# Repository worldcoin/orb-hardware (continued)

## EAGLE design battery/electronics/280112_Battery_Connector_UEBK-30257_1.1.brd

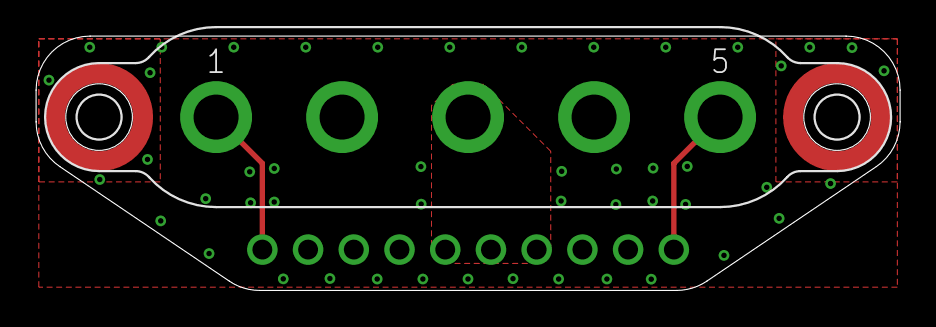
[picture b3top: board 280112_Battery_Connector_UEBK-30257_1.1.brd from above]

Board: 2 copper layers, 48.0 x 14.1 mm, 4 parts (1 on the bottom side), 4 nets.

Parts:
SPACER1, SPACER2: 9774010151; WA-SMSI_9774010151_WUERTH
X1: 61301011121; 61301011121_WUERTH
X2: UEBK-30257; UEBK-30257_UWE

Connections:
GND: SPACER1.2, SPACER1.3, SPACER2.2, SPACER2.3, X1.2, X1.3, X1.4, X1.8, X1.9, X2.2, X2.4
HOST_PRESENT: X1.1, X2.1
SMBUS_SDA/CAN/UART: X1.10, X2.5
V_PACK: X1.5, X1.6, X1.7, X2.3

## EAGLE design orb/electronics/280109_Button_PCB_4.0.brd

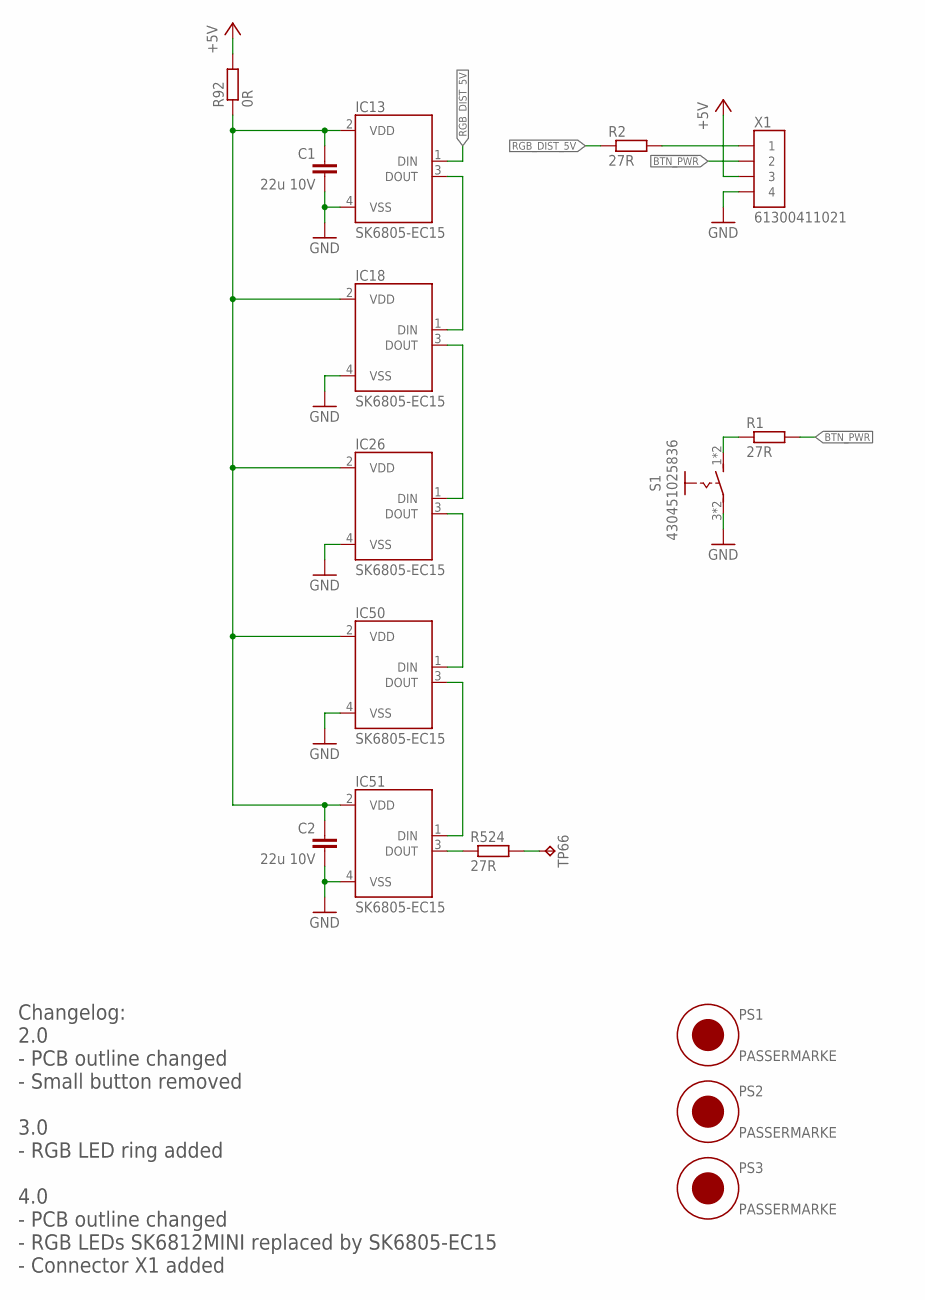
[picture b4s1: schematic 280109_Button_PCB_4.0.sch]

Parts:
C1, C2: 22u 10V; C0805; VOLTAGE 10.0 V
IC13, IC18, IC26, IC50, IC51: SK6805-EC15; SK6805-EC_IPIXEL
PS1, PS2, PS3: PASSERMARKE
R1, R2, R524: 27R; R0603
R92: 0R; R0603
S1: 430451025836; 430451025836_WUERTH
TP66: TESTPOINT_VIA_ROUND_0.8MM; TESTVIA_ROUND_0.8MM
X1: 61300411021; 61300411021_WUERTH

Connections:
!BTN_PWR: R1.2, X1.2
+5V: R92.2, X1.3
GND: C1.2, C2.2, IC13.4 (VSS), IC18.4 (VSS), IC26.4 (VSS), IC50.4 (VSS), IC51.4 (VSS), S1.3, S1.4, X1.4
unnamed: R1.1, S1.1 (S), S1.2 (S)
unnamed: R2.2, X1.1
unnamed: R524.2, TP66.P$1
unnamed: C1.1, C2.1, IC13.2 (VDD), IC18.2 (VDD), IC26.2 (VDD), IC50.2 (VDD), IC51.2 (VDD), R92.1
unnamed: IC51.3 (DOUT), R524.1
unnamed: IC50.3 (DOUT), IC51.1 (DIN)
unnamed: IC26.3 (DOUT), IC50.1 (DIN)
unnamed: IC18.3 (DOUT), IC26.1 (DIN)
unnamed: IC13.3 (DOUT), IC18.1 (DIN)
RGB_DIST_5V: IC13.1 (DIN), R2.1

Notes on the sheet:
Changelog: 2.0 - PCB outline changed - Small button removed 3.0 - RGB LED ring added 4.0 - PCB outline changed - RGB LEDs SK6812MINI replaced by SK6805-EC15 - Connector X1 added

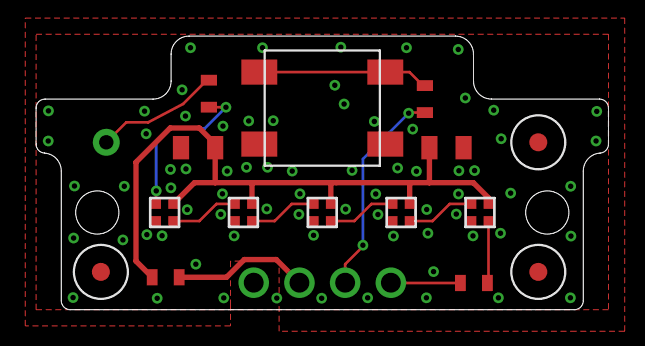
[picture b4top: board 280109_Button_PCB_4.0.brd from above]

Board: 2 copper layers, 31.8 x 15.2 mm, 17 parts (1 on the bottom side), 13 nets.

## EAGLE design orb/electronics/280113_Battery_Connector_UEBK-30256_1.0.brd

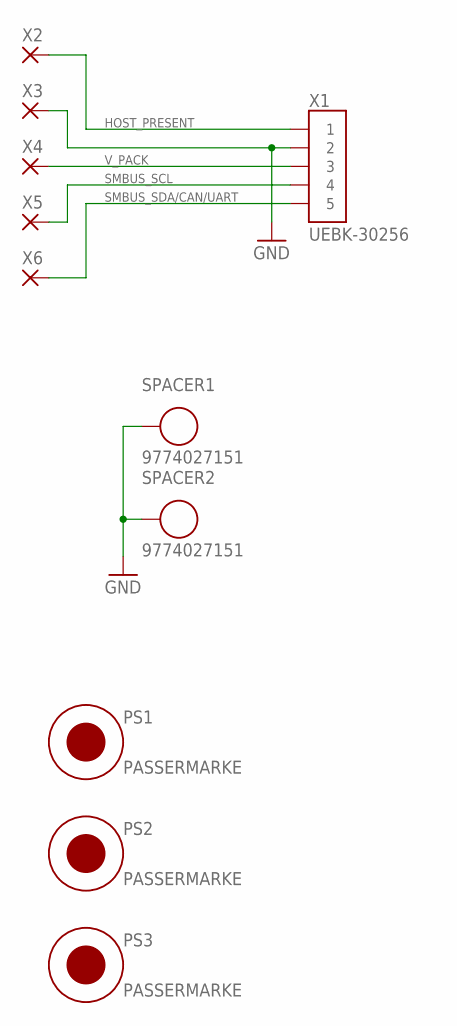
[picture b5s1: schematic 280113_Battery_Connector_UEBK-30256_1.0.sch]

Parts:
PS1, PS2, PS3: PASSERMARKE
SPACER1, SPACER2: 9774027151; WA-SMSI_9774027151_WUERTH
X1: UEBK-30256; UEBK-30256_UWE
X2, X3, X4, X5, X6: PAD_RECT_VIAS_3.3X10.0MM_TOP_BOT

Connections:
GND: SPACER1.2, SPACER1.3, SPACER2.2, SPACER2.3, X1.2, X3.1, X3.2, X3.P$1, X3.P$2, X3.P$3, X3.P$4, X3.P$5, X3.P$6, X3.P$7, X3.P$8, X3.P$9, X3.P$10, X3.P$11, X3.P$12, X3.P$13, X3.P$14, X3.P$15, X3.P$16, X3.P$17, X3.P$18, X3.P$19, X3.P$20, X3.P$21, X3.P$22, X3.P$23, X3.P$24, X3.P$25, X3.P$26, X3.P$27
HOST_PRESENT: X1.1, X2.1, X2.2, X2.P$1, X2.P$2, X2.P$3, X2.P$4, X2.P$5, X2.P$6, X2.P$7, X2.P$8, X2.P$9, X2.P$10, X2.P$11, X2.P$12, X2.P$13, X2.P$14, X2.P$15, X2.P$16, X2.P$17, X2.P$18, X2.P$19, X2.P$20, X2.P$21, X2.P$22, X2.P$23, X2.P$24, X2.P$25, X2.P$26, X2.P$27
SMBUS_SCL: X1.4, X5.1, X5.2, X5.P$1, X5.P$2, X5.P$3, X5.P$4, X5.P$5, X5.P$6, X5.P$7, X5.P$8, X5.P$9, X5.P$10, X5.P$11, X5.P$12, X5.P$13, X5.P$14, X5.P$15, X5.P$16, X5.P$17, X5.P$18, X5.P$19, X5.P$20, X5.P$21, X5.P$22, X5.P$23, X5.P$24, X5.P$25, X5.P$26, X5.P$27
SMBUS_SDA/CAN/UART: X1.5, X6.1, X6.2, X6.P$1, X6.P$2, X6.P$3, X6.P$4, X6.P$5, X6.P$6, X6.P$7, X6.P$8, X6.P$9, X6.P$10, X6.P$11, X6.P$12, X6.P$13, X6.P$14, X6.P$15, X6.P$16, X6.P$17, X6.P$18, X6.P$19, X6.P$20, X6.P$21, X6.P$22, X6.P$23, X6.P$24, X6.P$25, X6.P$26, X6.P$27
V_PACK: X1.3, X4.1, X4.2, X4.P$1, X4.P$2, X4.P$3, X4.P$4, X4.P$5, X4.P$6, X4.P$7, X4.P$8, X4.P$9, X4.P$10, X4.P$11, X4.P$12, X4.P$13, X4.P$14, X4.P$15, X4.P$16, X4.P$17, X4.P$18, X4.P$19, X4.P$20, X4.P$21, X4.P$22, X4.P$23, X4.P$24, X4.P$25, X4.P$26, X4.P$27

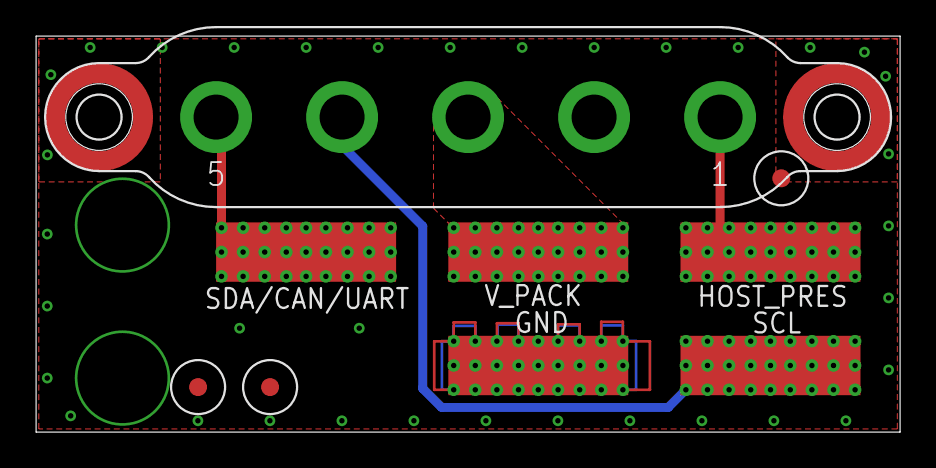
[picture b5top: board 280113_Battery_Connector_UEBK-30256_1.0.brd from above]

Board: 2 copper layers, 48.0 x 22.0 mm, 11 parts (0 on the bottom side), 5 nets.

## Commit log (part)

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2023-01-20 init
2023-01-20 Update README.md
    added link to blogpost; minor text refinements
2023-01-20 Fix LICENSE link
2023-01-27 updated engineering files
2023-01-27 Update README.md
    updated link to blogpost
2023-06-01 Fix typo
    Changed "including" to "include" in one instance, which is the right form in this case.
2023-07-18 Update LICENSE.md
    Fix broken link
2023-07-31 Update LICENSE.md
    Fix link of UN site.
2023-08-01 Fix typo
2024-03-14 updated electronics, BOM and descriptions to latest hardware design
2024-03-22 updated STEP files for battery and orb
2024-03-22 review and correction BOM
2024-03-25 remove .DS_Store files
    clean up repo
2024-03-25 gitignore: .DS_Store files
2024-07-19 Add .github/workflows/relyance-sci.yml
2024-09-27 Create Word fed
2024-12-24 Update relyance-sci.yml
    app_0534e0cad1d771cf670b8dd93815e28d
2025-03-14 docs: update readme
2025-05-08 Orb Fixes #21
2025-09-30 Create problem
2025-10-12 Update LICENSE.md
    บัญชีถูกจำกัด
